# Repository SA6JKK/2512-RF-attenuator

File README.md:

# 2512-attenuator
RF-attenuator from 1W 2512 size resistors with both BNC and SMA connectors. Works OK from DC to 30MHz. 

Measured with NanoVNA-H4 using NanoVNA saver.

---

## PCB Specs

PCB size: 71.5 x  25 x 1.6 mm

PCB Stackup: Two layer FR-4 (No impedance control) 

Traces are not 50 ohm as this is mainly for < 50 MHz use and the size of the entire PCB is thus significantly smaller than the wavelength at this frequency. 

I tried to only use resistors from the E12 series as much as possible.

Two parallel resistors are used for each position for increased thermal handling and to achieve a resistance closer to the calculated values.

---

## Heat Sink

Made to fit the following heat sink. 

> Heat Sink, 4.4 °C/W, TO-218, TO-220, TO-247, 42 mm, 38.1 mm, 25 mm

> Farnell Order code 1710612

---

## Design Notes

* Schematic is in the `plots` folder.
* [Link to RF Attenuator calculator](https://leleivre.com/rf_pipad.html)
* [Link to Parallel Resistor calculator](https://jansson.us/resistors.html)

Connections:
* `R1//R2//R3//R4` (input side, to ground)
* `R5//R6` (top of Pi network)
* `R7//R8//R9//R10` (output side, to ground)

---

## Resistor Values for Various Attenuators

| Resistor | Value for 1dB Attenuator | Value for 2dB Attenuator | Value for 3dB Attenuator | Value for 6dB Attenuator | Value for 10dB Attenuator | Value for 30dB Attenuator |
|----------|--------------------------|--------------------------|--------------------------|--------------------------|---------------------------|---------------------------|
| R1       | DNI                      | DNI                      | DNI                      | DNI                      | DNI                       | DNI                       |
| R2       | 2k2                      | 820                      | 560                      | 270                      | 180                       | 100                       |
| R3       | DNI                      | DNI                      | DNI                      | DNI                      | DNI                       | DNI                       |
| R4       | 1k5                      | 1k                       | 560                      | 330                      | 220                       | 120                       |
| R5       | 12                       | 22                       | 33                       | 68                       | 150                       | 1.5k                      |
| R6       | 10                       | 24                       | 39                       | 82                       | 150                       | 1.8k                      |
| R7       | 2k2                      | 1k                       | 560                      | 270                      | 180                       | 100                       |
| R8       | 1k5                      | 820                      | 560                      | 330                      | 220                       | 120                       |
| R9       | DNI                      | DNI                      | DNI                      | DNI                      | DNI                       | DNI                       |
| R10      | DNI                      | DNI                      | DNI                      | DNI                      | DNI                       | DNI                       |

DNI = Do Not Install

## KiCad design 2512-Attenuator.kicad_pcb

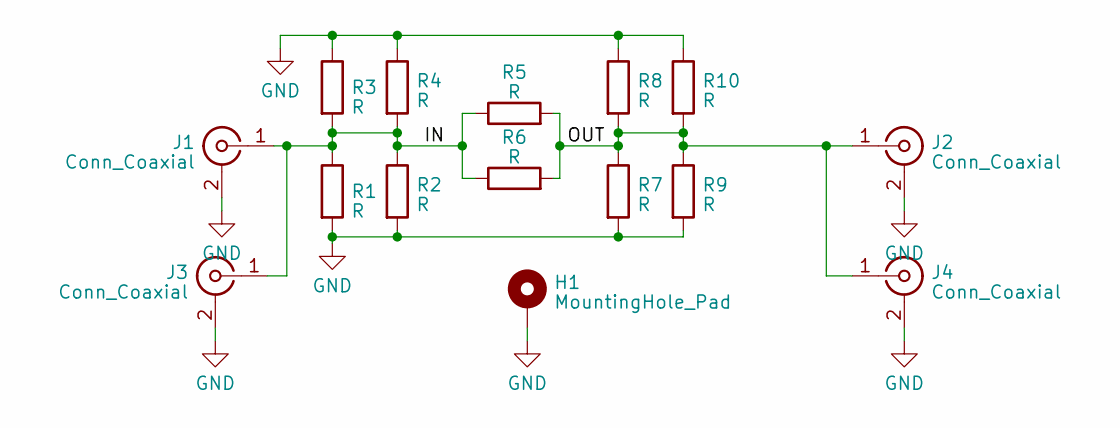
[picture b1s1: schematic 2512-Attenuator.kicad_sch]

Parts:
H1: MountingHole_Pad; MountingHole_3.2mm_M3_Pad_Via
J1, J2: Conn_Coaxial; BNC_Amphenol_B6252HB-NPP3G-50_Horizontal
J3, J4: Conn_Coaxial; SMA_Amphenol_901-143_Horizontal
R1, R2, R3, R4, R5, R6, R7, R8, R9, R10: R; R_2512_6332Metric_Pad1.40x3.35mm_HandSolder

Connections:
/IN: J1.1 (In), J3.1 (In), R1.1, R2.1, R3.2, R4.2, R5.1, R6.1
/OUT: J2.1 (In), J4.1 (In), R5.2, R6.2, R7.1, R8.2, R9.1, R10.2
GND: H1.1, J1.2 (Ext), J2.2 (Ext), J3.2 (Ext), J4.2 (Ext), R1.2, R2.2, R3.1, R4.1, R7.2, R8.1, R9.2, R10.1

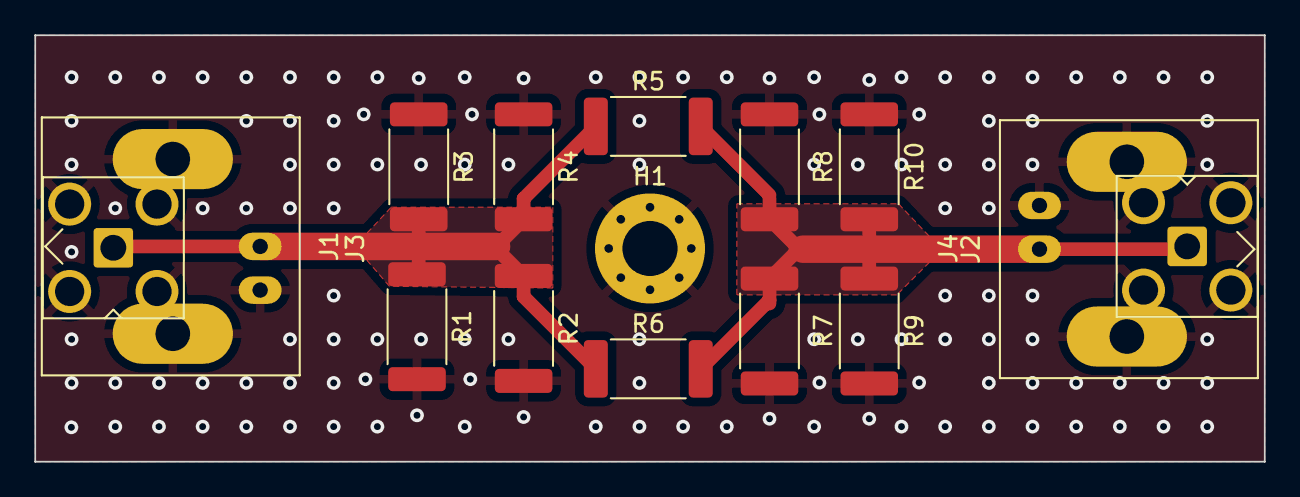
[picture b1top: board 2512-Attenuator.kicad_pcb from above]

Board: 2 copper layers, 71.5 x 24.8 mm, 15 parts (0 on the bottom side), 3 nets.

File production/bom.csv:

Designator,Footprint,Quantity,Value,LCSC Part #
H1,MountingHole_3.2mm_M3_Pad_Via,1,MountingHole_Pad,
"J1, J2",BNC_Amphenol_B6252HB-NPP3G-50_Horizontal,2,Conn_Coaxial,
"J3, J4",SMA_Amphenol_901-143_Horizontal,2,Conn_Coaxial,
"R1, R10, R2, R3, R4, R5, R6, R7, R8, R9",2512,10,R,

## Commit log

2023-04-29 Add KiCad Files
    Schematic, layout, plots and JLC-PCB production files
2023-04-29 Added BoM for 1,2,3,6,10 dB attenuation
2023-04-29 Updated Readme formatting
2023-05-13 Add s-parameter plot
2023-05-13 Update README.md with plots
2023-05-13 Minor Update README.md
2023-05-13 Create MIT LICENSE
2023-05-20 Updated plots with correct legend
2023-05-20 Update graphs attempt 2
2023-05-20 Change graphs to correct legend attempt 3
2023-07-24 Update README.md with PCB info
    Adds more PCB info and link to attenuator calculator
2023-08-09 Convert resistor values to table
2023-08-09 Add 30dB values to table
2023-08-09 Improve doc format and design notes
2023-08-09 Updated 30 dB attenuator resistor values
    30 dB attenuation require around 53 ohm to GND and 790 ohm in series. Earlier commit had this opposite way around.
    Parallel resistors for 30 dB changed to be have resistance values closer together to better distribute the heat generated in them.
